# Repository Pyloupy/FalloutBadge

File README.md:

A cool badge made in the Fallout Event of Hack Club in Shenzhen!
It's in a cool form of a koi fish and his eye lights up!

Here's the schematic:

PCB:

And 3d view!

My slack username : Pylou

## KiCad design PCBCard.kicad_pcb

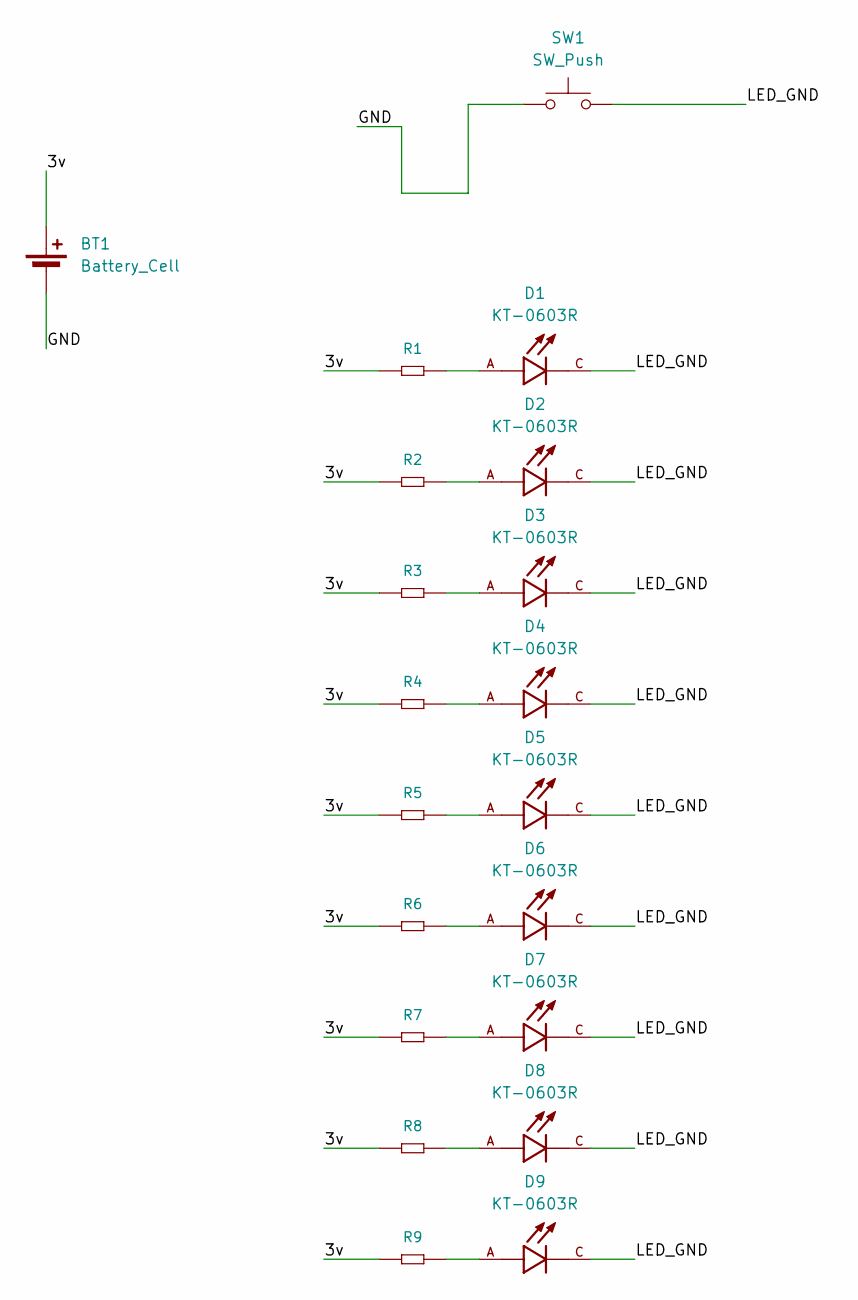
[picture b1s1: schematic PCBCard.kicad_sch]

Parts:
BT1: Battery_Cell; BatteryHolder_Keystone_106_1x20mm
D1, D2, D3, D4, D5, D6, D7, D8, D9: KT-0603R; LED_KT-0603R; PARTREV 2013/01/24
R1, R2, R3, R4, R5, R6, R7, R8, R9: SMD-RES-0R-5%-1_10W_0603_; R_Axial_DIN0207_L6.3mm_D2.5mm_P2.54mm_Vertical; MPN RC0603JR-070RL
SW1: SW_Push; SW_Slide_SPDT_Straight_CK_OS102011MS2Q

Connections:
/3v: BT1.1 (+), R1.1, R2.1, R3.1, R4.1, R5.1, R6.1, R7.1, R8.1, R9.1
/GND: BT1.2 (-), SW1.1
/LED_GND: D1.C, D2.C, D3.C, D4.C, D5.C, D6.C, D7.C, D8.C, D9.C, SW1.2
unnamed: D1.A, R1.2
unnamed: D2.A, R2.2
unnamed: D3.A, R3.2
unnamed: D4.A, R4.2
unnamed: D5.A, R5.2
unnamed: D6.A, R6.2
unnamed: D7.A, R7.2
unnamed: D8.A, R8.2
unnamed: D9.A, R9.2

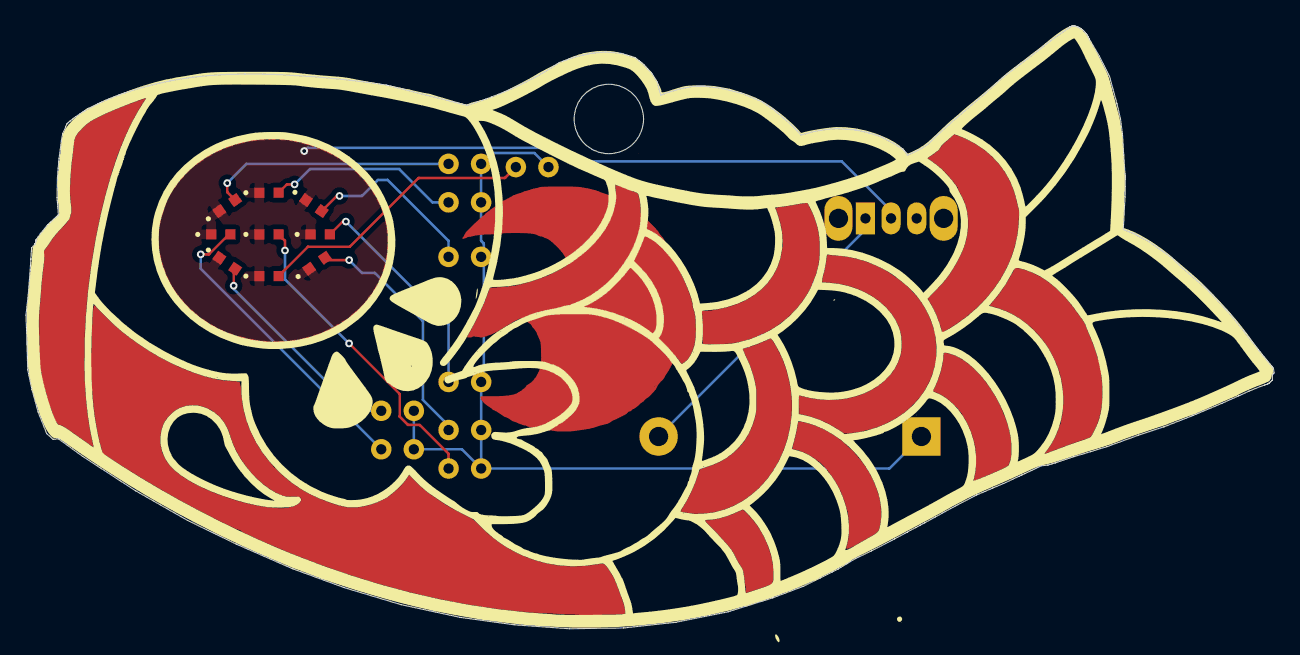
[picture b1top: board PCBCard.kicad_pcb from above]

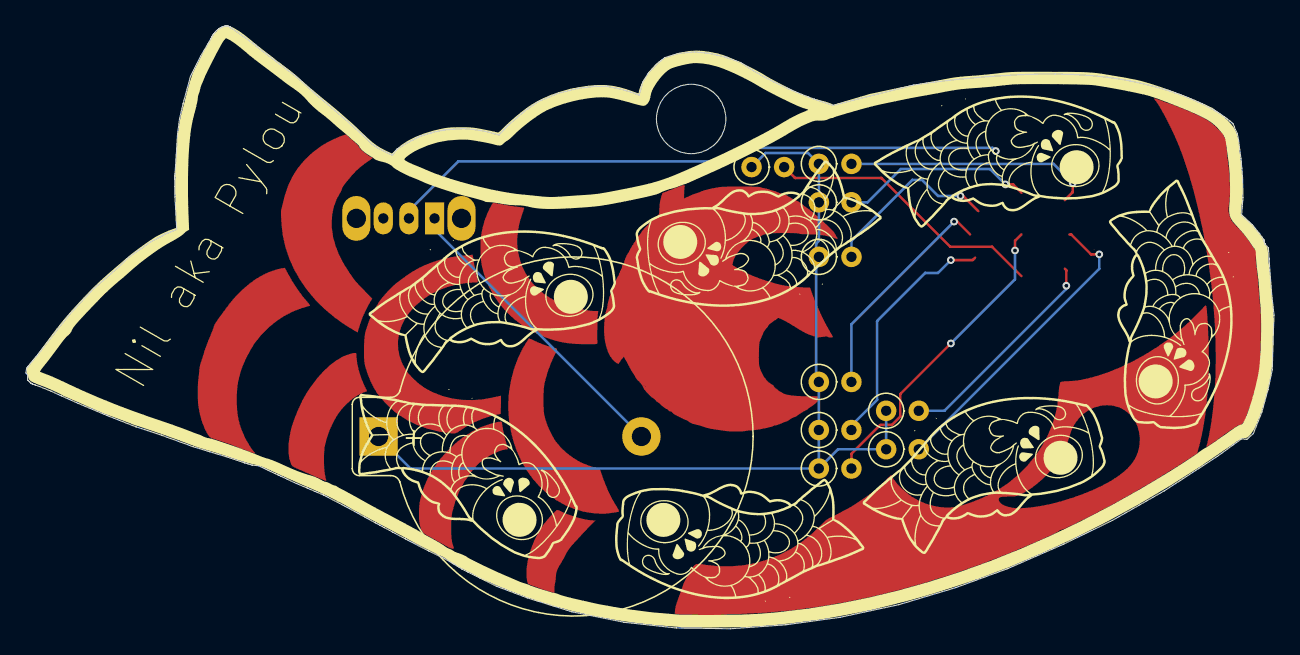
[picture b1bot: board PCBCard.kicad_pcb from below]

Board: 2 copper layers, 97.3 x 47.0 mm, 20 parts (10 on the bottom side), 12 nets.
